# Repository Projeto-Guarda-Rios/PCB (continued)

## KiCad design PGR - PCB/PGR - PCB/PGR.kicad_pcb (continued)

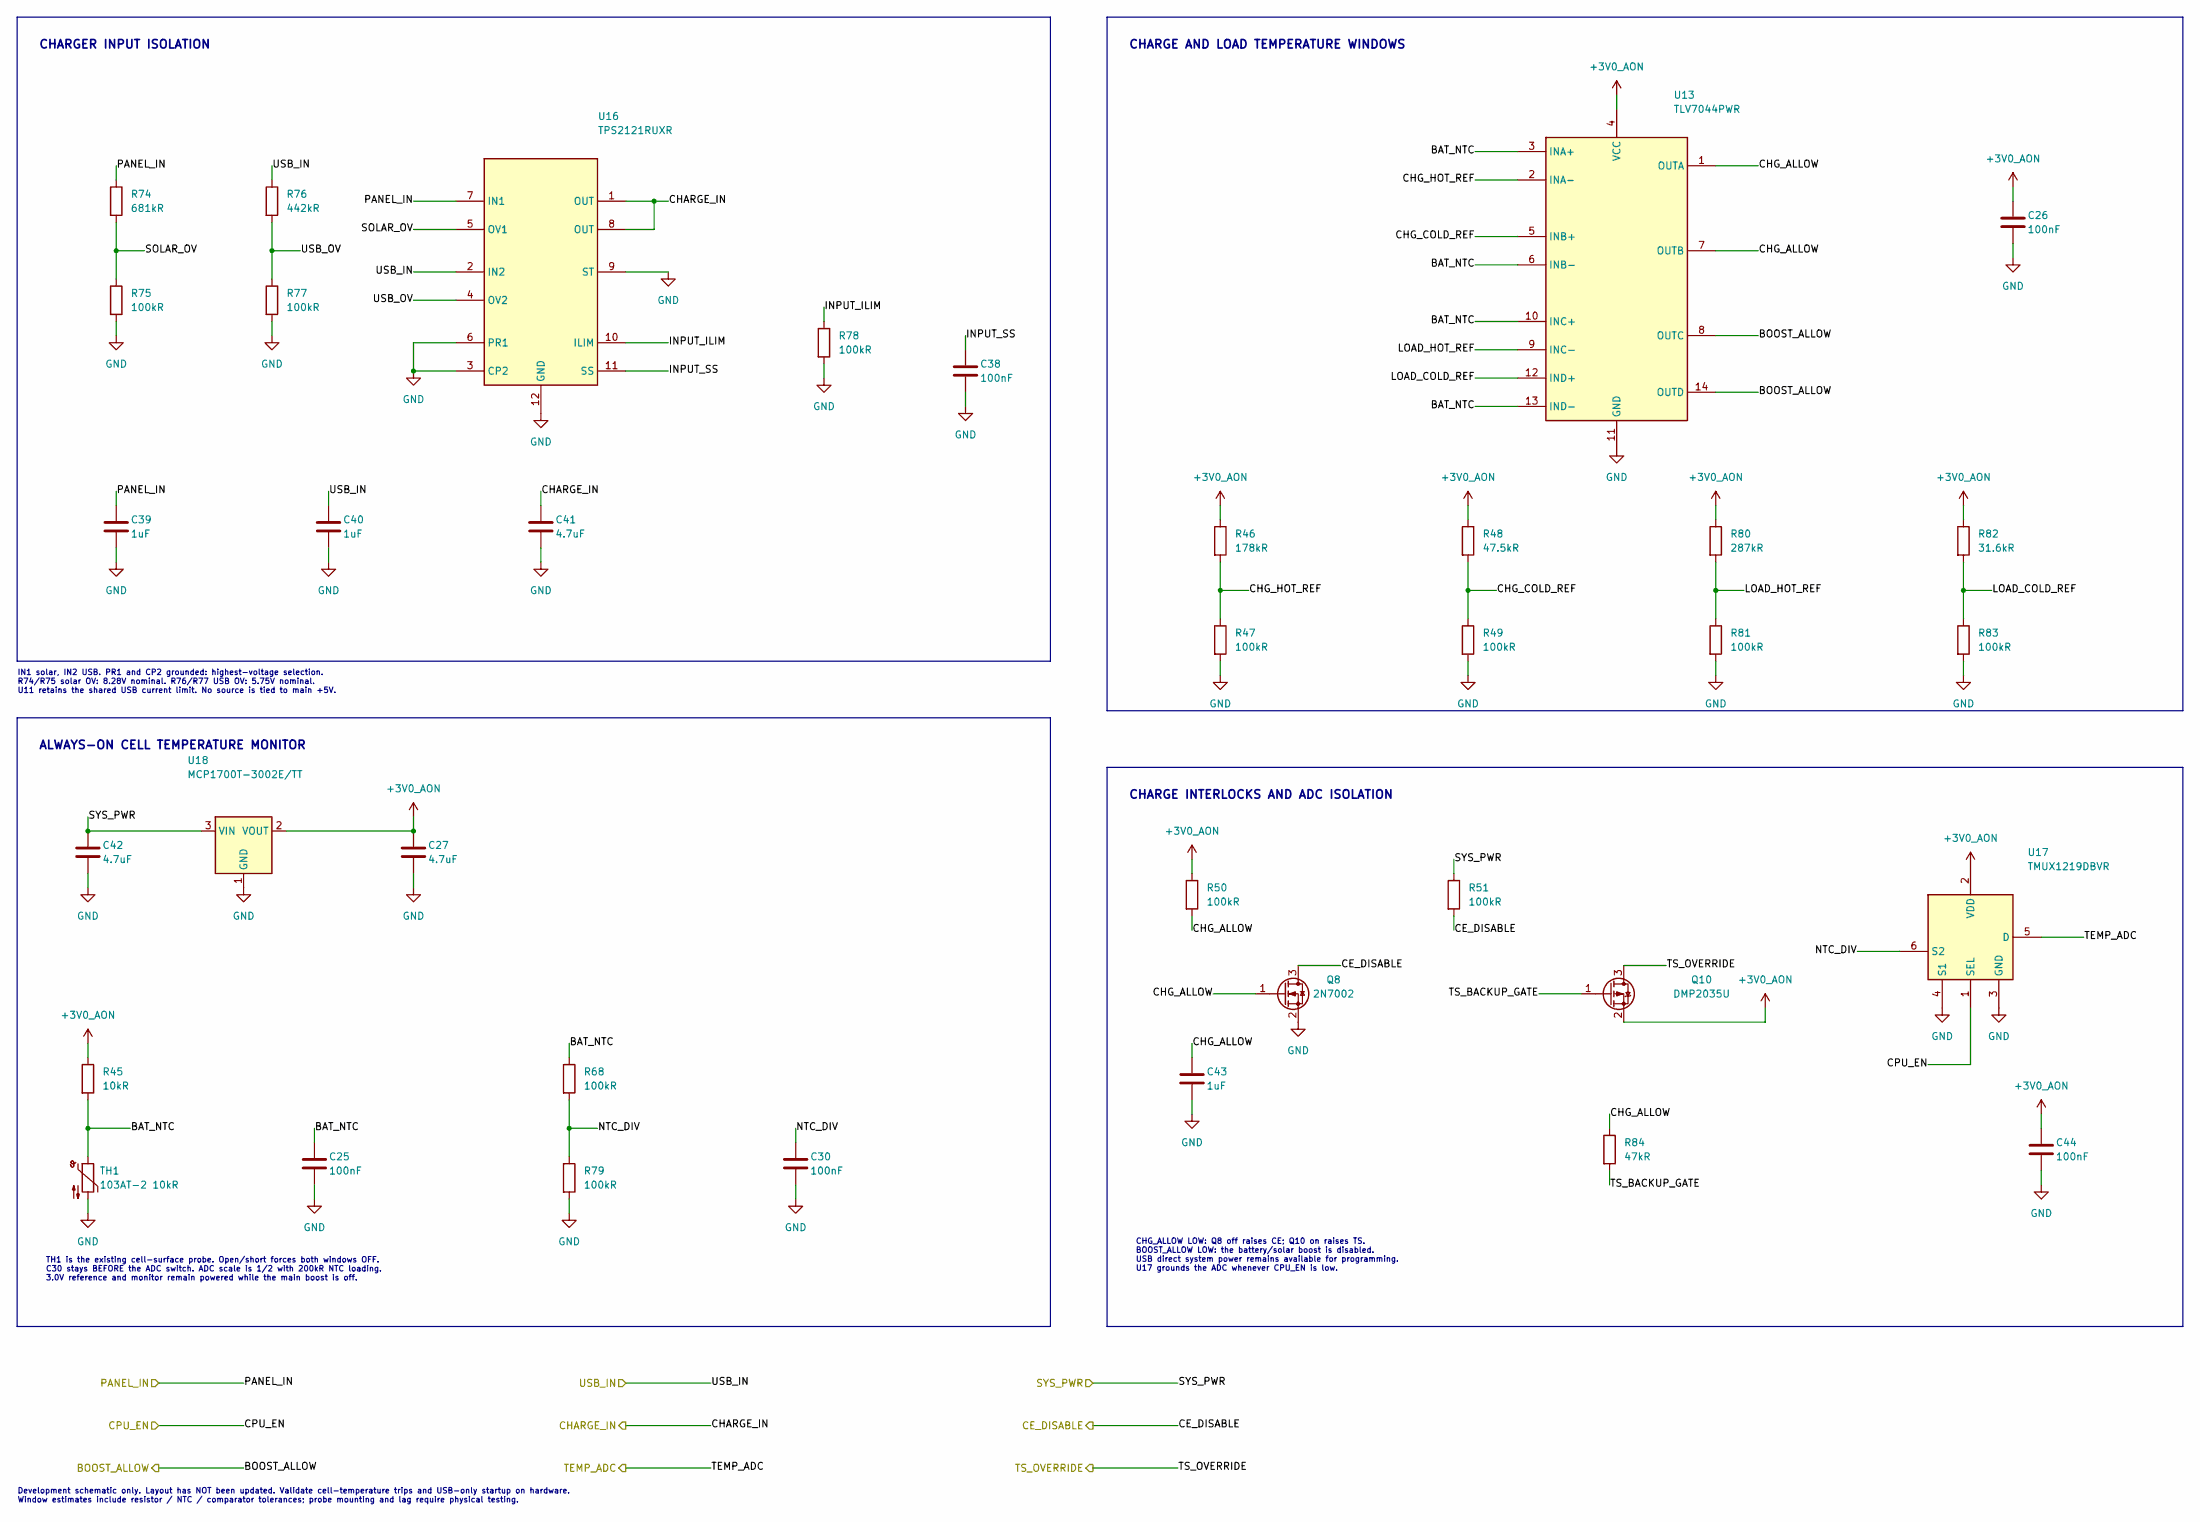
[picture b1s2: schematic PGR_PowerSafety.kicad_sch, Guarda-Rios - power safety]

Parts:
C25, C26, C30, C38, C44: 100nF; C_0603_1608Metric; Voltage Rating 16V minimum; Tolerance 10%
C27, C41, C42: 4.7uF; C_0805_2012Metric; Voltage Rating 10V minimum; Tolerance 10%
C39, C40, C43: 1uF; C_0805_2012Metric; Voltage Rating 10V minimum; Tolerance 10%
Q8: 2N7002; SOT-23; MPN 2N7002-7-F
Q10: DMP2035U; SOT-23; MPN DMP2035U-7
R45: 10kR; R_0603_1608Metric; Tolerance 0.1%; Power Rating 0.1W minimum
R46: 178kR; R_0603_1608Metric; Tolerance 0.1%; Power Rating 0.1W minimum
R47, R49, R68, R75, R77, R79, R81, R83: 100kR; R_0603_1608Metric; Tolerance 0.1%; Power Rating 0.1W minimum
R48: 47.5kR; R_0603_1608Metric; Tolerance 0.1%; Power Rating 0.1W minimum
R50, R51, R78: 100kR; R_0603_1608Metric; Tolerance 1%; Power Rating 0.1W minimum
R74: 681kR; R_0603_1608Metric; Tolerance 0.1%; Power Rating 0.1W minimum
R76: 442kR; R_0603_1608Metric; Tolerance 0.1%; Power Rating 0.1W minimum
R80: 287kR; R_0603_1608Metric; Tolerance 0.1%; Power Rating 0.1W minimum
R82: 31.6kR; R_0603_1608Metric; Tolerance 0.1%; Power Rating 0.1W minimum
R84: 47kR; R_0603_1608Metric; Tolerance 1%; Power Rating 0.1W minimum
TH1: 103AT-2 10kR; NTC_Semitec_103AT-2_P2.54mm; R25 Tolerance 1%; MPN 103AT-2; LCSC C5346323
U13: TLV7044PWR; TSSOP-14_4.4x5mm_P0.65mm; MPN TLV7044PWR
U16: TPS2121RUXR; Texas_VQFN-HR-12_2x2.5mm_P0.5mm; MPN TPS2121RUXR
U17: TMUX1219DBVR; SOT-23-6; MPN TMUX1219DBVR
U18: MCP1700T-3002E/TT; SOT-23; MPN MCP1700T-3002E/TT

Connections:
+3V0_AON: C26.1, C27.1, C44.1, Q10.2 (S), R45.1, R46.1, R48.1, R50.1, R80.1, R82.1, U13.4 (VCC), U17.2 (VDD), U18.2 (VOUT)
/Power safety/BAT_NTC: C25.1, R45.2, R68.1, TH1.1, U13.3 (INA+), U13.6 (INB-), U13.10 (INC+), U13.13 (IND-)
/Power safety/CHG_ALLOW: C43.1, Q8.1 (G), R50.2, R84.1, U13.1 (OUTA), U13.7 (OUTB)
/Power safety/CHG_COLD_REF: R48.2, R49.1, U13.5 (INB+)
/Power safety/CHG_HOT_REF: R46.2, R47.1, U13.2 (INA-)
/Power safety/INPUT_ILIM: R78.1, U16.10 (ILIM)
/Power safety/INPUT_SS: C38.1, U16.11 (SS)
/Power safety/LOAD_COLD_REF: R82.2, R83.1, U13.12 (IND+)
/Power safety/LOAD_HOT_REF: R80.2, R81.1, U13.9 (INC-)
/Power safety/NTC_DIV: C30.1, R68.2, R79.1, U17.6 (S2)
/Power safety/SOLAR_OV: R74.2, R75.1, U16.5 (OV1)
/Power safety/TS_BACKUP_GATE: Q10.1 (G), R84.2
/Power safety/USB_OV: R76.2, R77.1, U16.4 (OV2)
BOOST_EN: U13.8 (OUTC), U13.14 (OUTD); also elsewhere on the board
CHARGER_IN: C41.1, U16.1 (OUT), U16.8 (OUT); also elsewhere on the board
CHG_CE: Q8.3 (D), R51.2; also elsewhere on the board
EN: U17.1 (SEL); also elsewhere on the board
GND: C25.2, C26.2, C27.2, C30.2, C38.2, C39.2, C40.2, C41.2, C42.2, C43.2, C44.2, Q8.2 (S), R47.2, R49.2, R75.2, R77.2, R78.2, R79.2, R81.2, R83.2, TH1.2, U13.11 (GND), U16.3 (CP2), U16.6 (PR1), U16.9 (ST), U16.12 (GND), U17.3 (GND), U17.4 (S1), U18.1 (GND); also elsewhere on the board
NTC_ADC: U17.5 (D); also elsewhere on the board
PWR_OUT: C42.1, R51.1, U18.3 (VIN); also elsewhere on the board
SOLAR_PROTECTED: C39.1, R74.1, U16.7 (IN1); also elsewhere on the board
TS_FIXED: Q10.3 (D); also elsewhere on the board
USB_LIMIT: C40.1, R76.1, U16.2 (IN2); also elsewhere on the board

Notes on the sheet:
CHARGE INTERLOCKS AND ADC ISOLATION
CHARGE AND LOAD TEMPERATURE WINDOWS
IN1 solar, IN2 USB. PR1 and CP2 grounded: highest-voltage selection. R74/R75 solar OV: 8.28V nominal. R76/R77 USB OV: 5.75V nominal. U11 retains the shared USB current limit. No source is tied to main +5V.
TH1 is the existing cell-surface probe. Open/short forces both windows OFF. C30 stays BEFORE the ADC switch. ADC scale is 1/2 with 200kR NTC loading. 3.0V reference and monitor remain powered while the main boost is off.
CHG_ALLOW LOW: Q8 off raises CE; Q10 on raises TS. BOOST_ALLOW LOW: the battery/solar boost is disabled. USB direct system power remains available for programming. U17 grounds the ADC whenever CPU_EN is low.
CHARGER INPUT ISOLATION
ALWAYS-ON CELL TEMPERATURE MONITOR
Development schematic only. Layout has NOT been updated. Validate cell-temperature trips and USB-only startup on hardware. Window estimates include resistor / NTC / comparator tolerances; probe mounting and lag require physical testing.

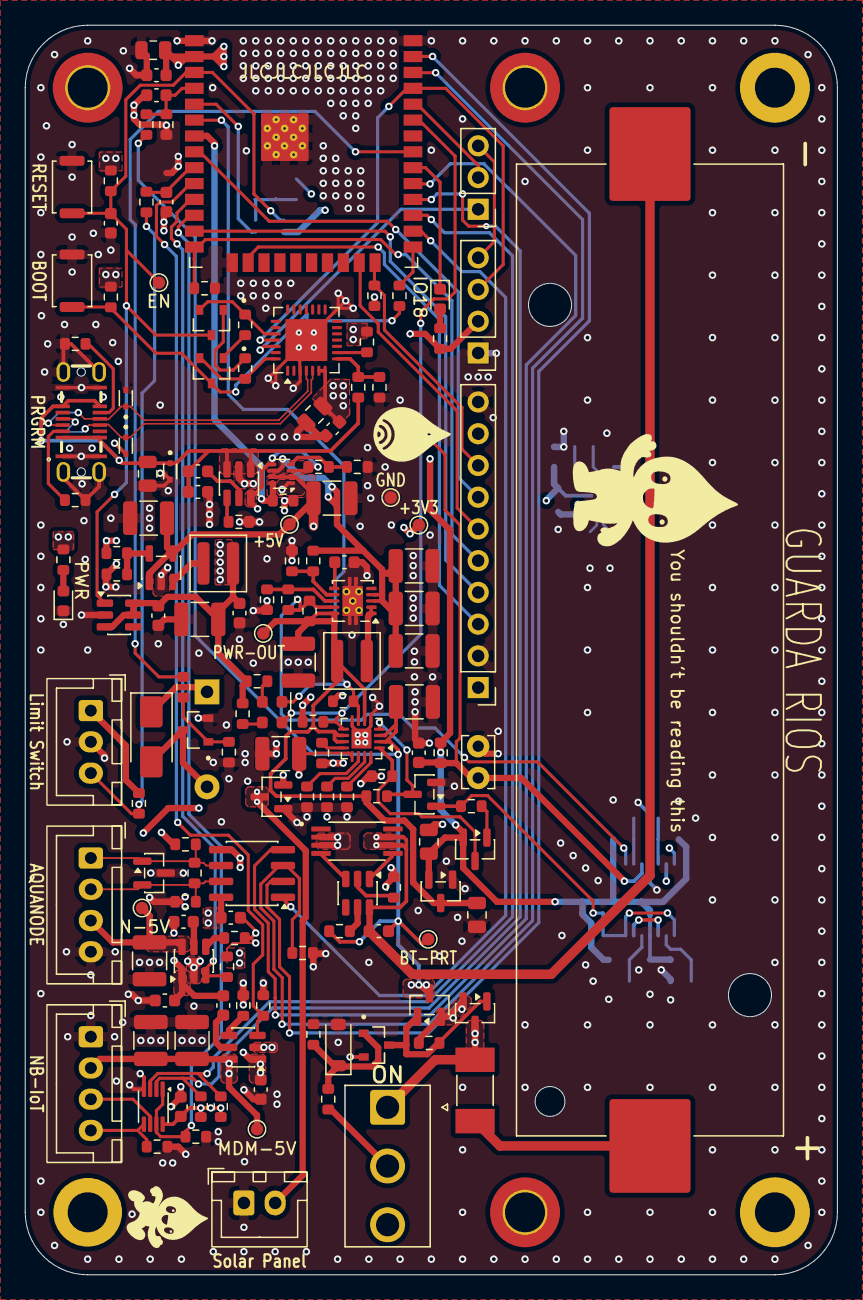
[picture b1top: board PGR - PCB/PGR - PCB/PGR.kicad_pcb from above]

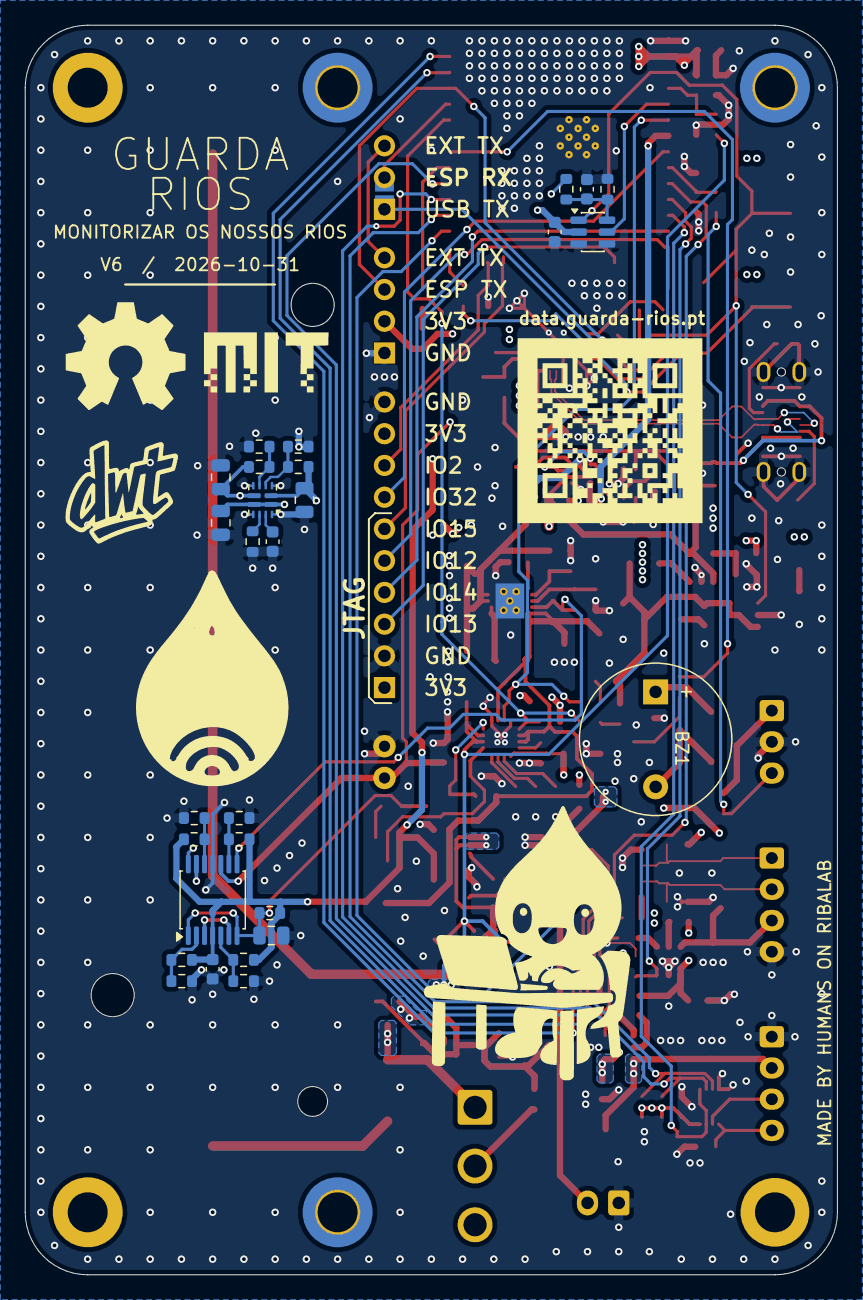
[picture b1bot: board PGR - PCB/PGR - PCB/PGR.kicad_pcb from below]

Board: 4 copper layers, 65.0 x 100.0 mm, 188 parts (29 on the bottom side), 108 nets.

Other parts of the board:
H1, H2, H5: MountingHole_3.2mm_M3_DIN965_Pad_TopBottom
H3, H6: MountingHole_3.2mm_M3_DIN965_Pad
H4: MountingHole_3.2mm_M3_ISO14580_Pad

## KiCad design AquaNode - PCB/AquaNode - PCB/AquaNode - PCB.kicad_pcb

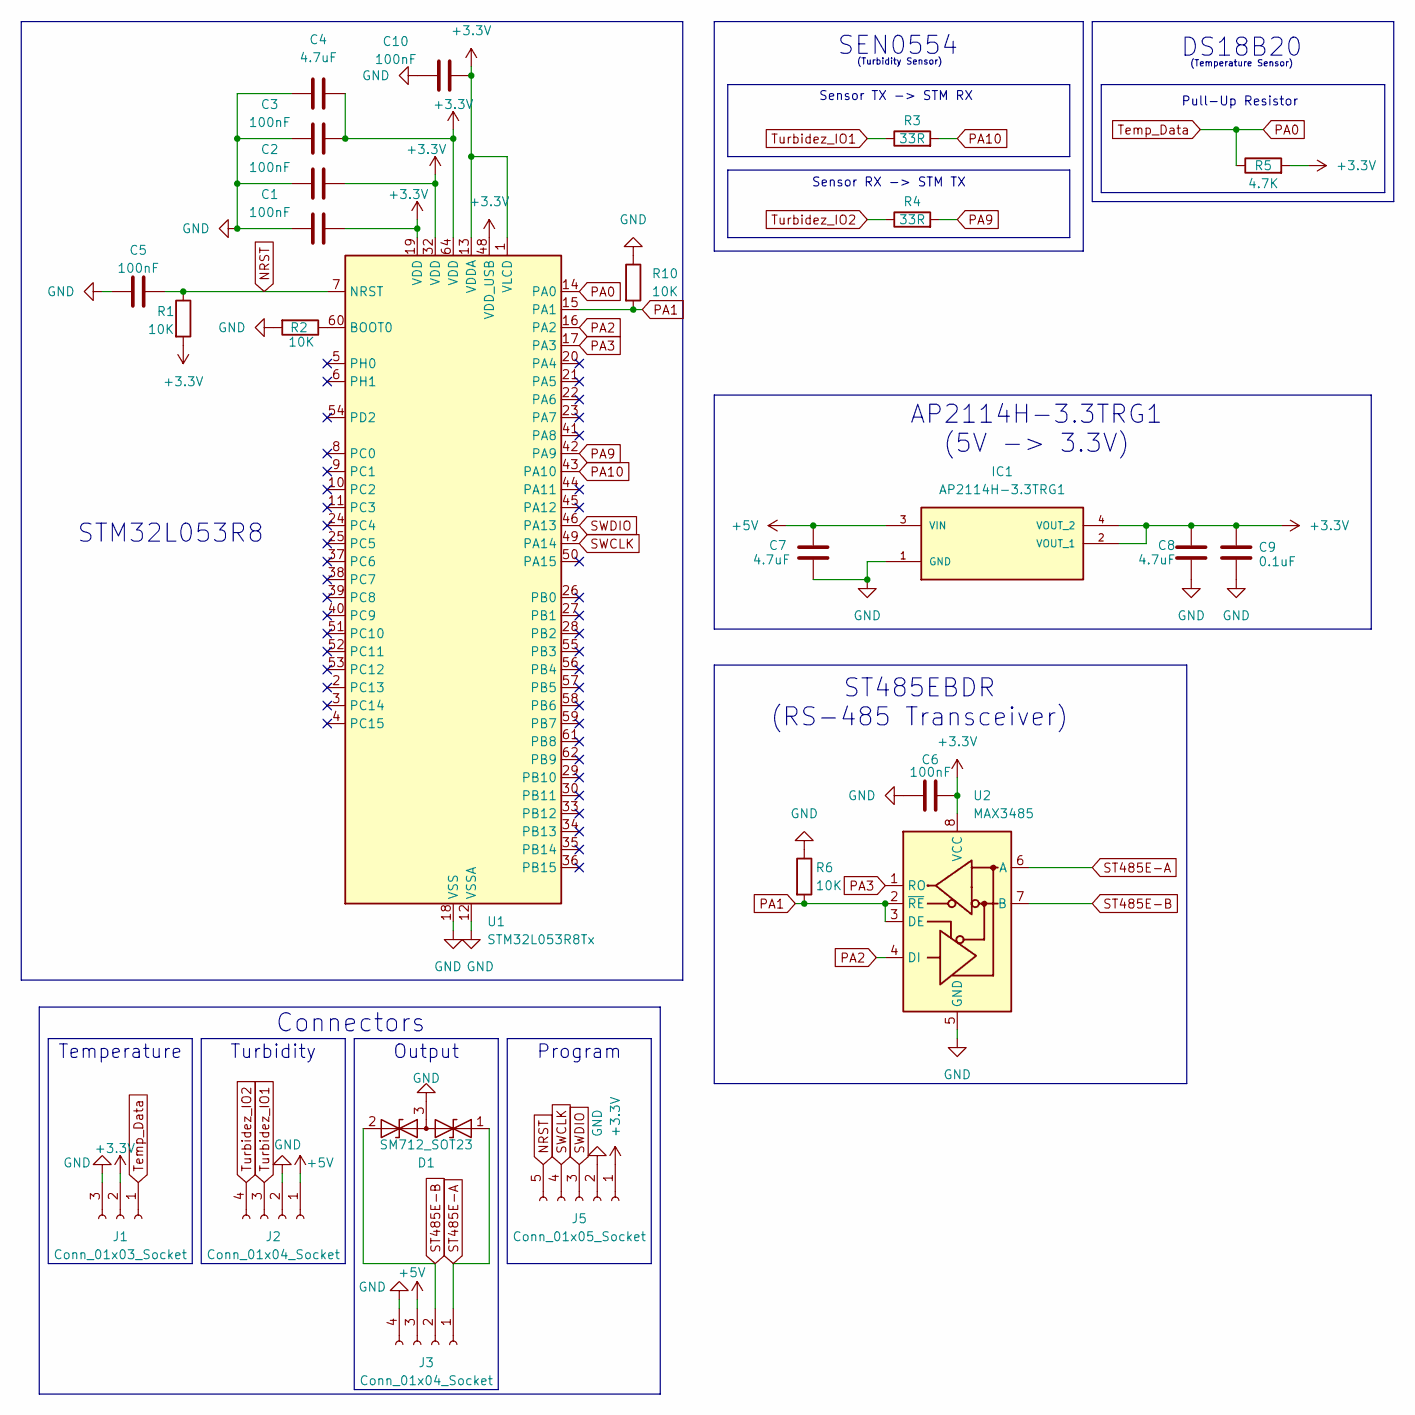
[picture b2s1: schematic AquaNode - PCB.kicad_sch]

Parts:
C1, C2, C3, C5, C6, C10: 100nF; C_0603_1608Metric
C4, C7, C8: 4.7uF; C_0603_1608Metric
C9: 0.1uF; C_0603_1608Metric
D1: SM712_SOT23; SOT-23
IC1: AP2114H-3.3TRG1; SOT230P700X180-4N; MANUFACTURER_PART_NUMBER AP2114H-3.3TRG1
J1: Conn_01x03_Socket; JST_EH_B3B-EH-A_1x03_P2.50mm_Vertical
J2, J3: Conn_01x04_Socket; JST_EH_B4B-EH-A_1x04_P2.50mm_Vertical
J5: Conn_01x05_Socket; PinHeader_1x05_P2.54mm_Vertical
R1, R2, R6, R10: 10K; R_0603_1608Metric
R3, R4: 33R; R_0603_1608Metric
R5: 4.7K; R_0603_1608Metric
U1: STM32L053R8Tx; LQFP-64_10x10mm_P0.5mm
U2: MAX3485; SOIC-8_3.9x4.9mm_P1.27mm

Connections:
+3.3V: C1.2, C2.2, C3.2, C4.2, C6.2, C8.1, C9.1, C10.2, IC1.2 (VOUT_1), IC1.4 (VOUT_2), J1.2, J5.1, R1.2, R5.2, U1.1 (VLCD), U1.13 (VDDA), U1.19 (VDD), U1.32 (VDD), U1.48 (VDD_USB), U1.64 (VDD), U2.8 (VCC)
+5V: C7.1, IC1.3 (VIN), J2.1, J3.3
GND: C1.1, C2.1, C3.1, C4.1, C5.1, C6.1, C7.2, C8.2, C9.2, C10.1, D1.3 (common), IC1.1 (GND), J1.3, J2.2, J3.4, J5.2, R2.2, R6.1, R10.1, U1.12 (VSSA), U1.18 (VSS), U1.31 (VSS), U1.47 (VSS), U1.63 (VSS), U2.5 (GND)
NRST: C5.2, J5.5, R1.1, U1.7 (NRST)
unnamed: R2.1, U1.60 (BOOT0)
PA0: J1.1, R5.1, U1.14 (PA0)
PA1: R6.2, R10.2, U1.15 (PA1), U2.2 (~RE), U2.3 (DE)
PA2: U1.16 (PA2), U2.4 (DI)
PA3: U1.17 (PA3), U2.1 (RO)
PA9: R4.2, U1.42 (PA9)
PA10: R3.2, U1.43 (PA10)
ST485E-A: D1.1 (A1), J3.1, U2.6 (A)
ST485E-B: D1.2 (A2), J3.2, U2.7 (B)
SWCLK: J5.4, U1.49 (PA14)
SWDIO: J5.3, U1.46 (PA13)
Turbidez_IO1: J2.3, R3.1
Turbidez_IO2: J2.4, R4.1

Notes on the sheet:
ST485EBDR (RS-485 Transceiver)
AP2114H-3.3TRG1 (5V -> 3.3V)
Program
DS18B20
Sensor RX -> STM TX
Output
Pull-Up Resistor
Connectors
Sensor TX -> STM RX
Temperature
SEN0554
(Temperature Sensor)
STM32L053R8
Turbidity
(Turbidity Sensor)

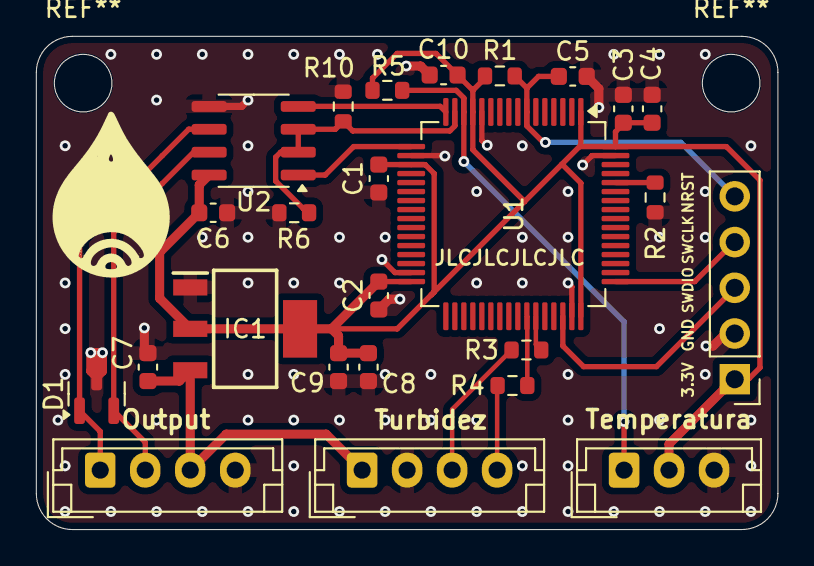
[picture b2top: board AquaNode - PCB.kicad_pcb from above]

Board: 2 copper layers, 41.2 x 27.4 mm, 25 parts (0 on the bottom side), 17 nets.

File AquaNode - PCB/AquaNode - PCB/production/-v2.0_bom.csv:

Designator,Footprint,Quantity,Value,LCSC Part #
"C1, C10, C2, C3, C5, C6",0603,6,100nF,
"C4, C7, C8",0603,3,4.7uF,
C9,0603,1,0.1uF,
D1,SOT-23,1,SM712_SOT23,
IC1,SOT230P700X180-4N,1,AP2114H-3.3TRG1,
J1,JST_EH_B3B-EH-A_1x03_P2.50mm_Vertical,1,Conn_01x03_Socket,
"J2, J3",JST_EH_B4B-EH-A_1x04_P2.50mm_Vertical,2,Conn_01x04_Socket,
J5,PinHeader_1x05_P2.54mm_Vertical,1,Conn_01x05_Socket,
"R1, R10, R2, R6",0603,4,10K,
R3,0603,1,1.8K,
R4,0603,1,3.3K,
R5,0603,1,4.7K,
U1,LQFP-64_10x10mm_P0.5mm,1,STM32L053R8Tx,
U2,SOIC-8_3.9x4.9mm_P1.27mm,1,MAX3485,

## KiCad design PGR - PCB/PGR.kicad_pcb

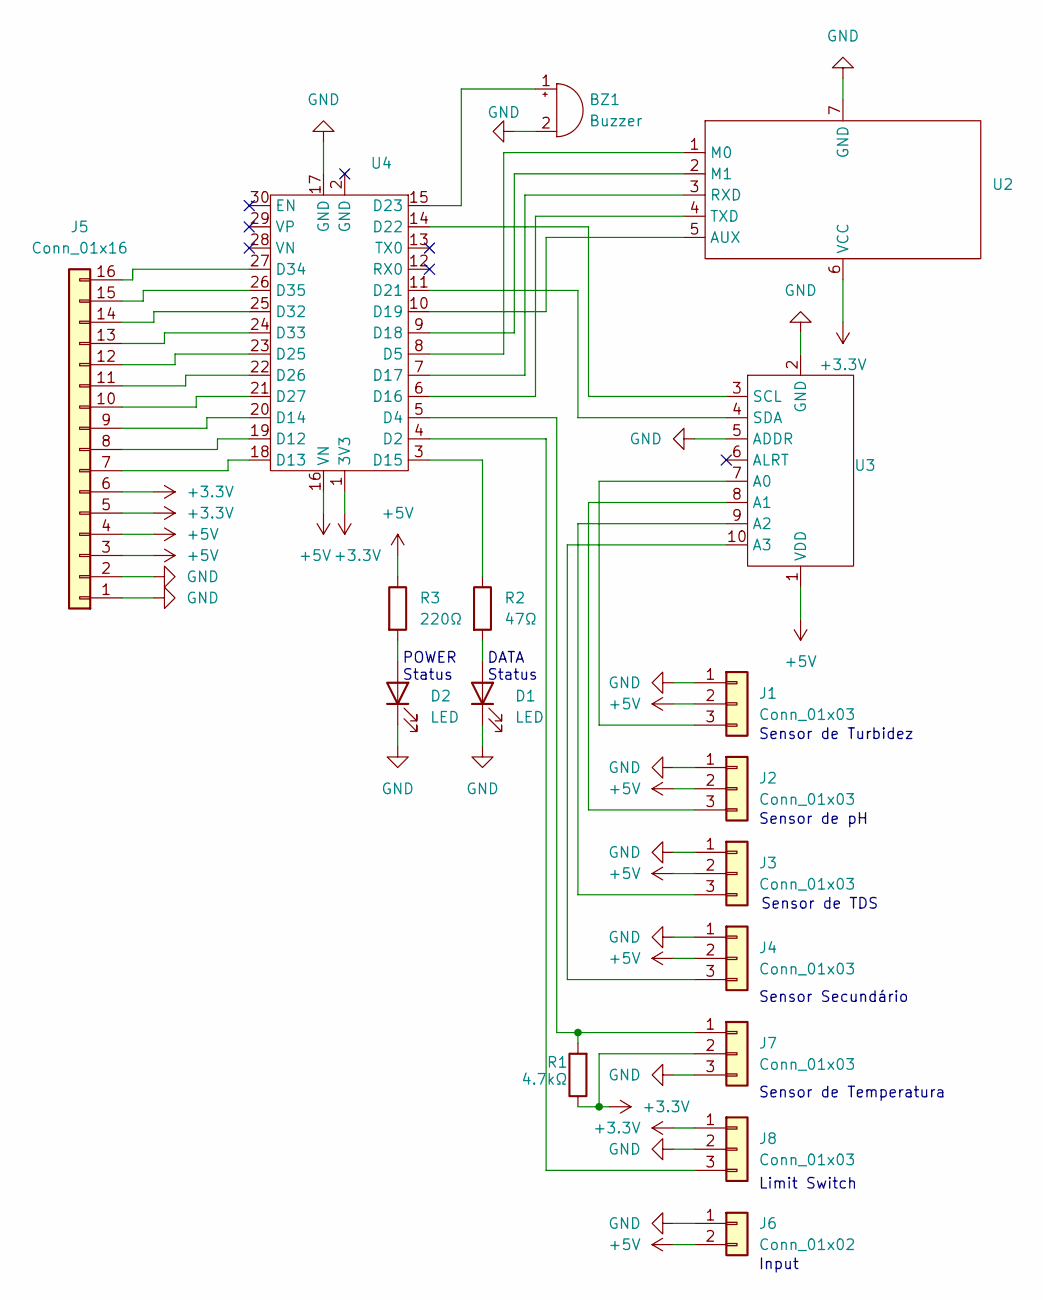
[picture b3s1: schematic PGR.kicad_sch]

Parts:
BZ1: Buzzer; Buzzer_12x9.5RM7.6
D1, D2: LED; LED_D3.0mm
J1, J2, J3, J4, J7, J8: Conn_01x03; JST_XH_B3B-XH-A_1x03_P2.50mm_Vertical
J5: Conn_01x16; PinSocket_1x16_P2.00mm_Vertical
J6: Conn_01x02; JST_XH_B2B-XH-A_1x02_P2.50mm_Vertical
R1: 4.7kΩ; R_Axial_DIN0204_L3.6mm_D1.6mm_P5.08mm_Horizontal
R2: 47Ω; R_Axial_DIN0204_L3.6mm_D1.6mm_P5.08mm_Horizontal
R3: 220Ω; R_Axial_DIN0204_L3.6mm_D1.6mm_P5.08mm_Horizontal
U2: PE32-90030D
U3: Adafruit_ADS1115
U4: ESP32-WROOM-32D - Board

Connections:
+3.3V: J5.5, J5.6, J7.2, J8.1, R1.1, U2.6 (VCC), U4.1 (3V3)
+5V: J1.2, J2.2, J3.2, J4.2, J5.3, J5.4, J6.2, R3.1, U3.1 (VDD), U4.16 (VN)
GND: BZ1.2 (-), D1.1 (K), D2.1 (K), J1.1, J2.1, J3.1, J4.1, J5.1, J5.2, J6.1, J7.3, J8.2, U2.7 (GND), U3.2 (GND), U3.5 (ADDR), U4.17 (GND)
unnamed: BZ1.1 (+), U4.15 (D23)
unnamed: D1.2 (A), R2.2
unnamed: D2.2 (A), R3.2
unnamed: J1.3, U3.7 (A0)
unnamed: J2.3, U3.8 (A1)
unnamed: J3.3, U3.9 (A2)
unnamed: J4.3, U3.10 (A3)
unnamed: J5.7, U4.18 (D13)
unnamed: J5.8, U4.19 (D12)
unnamed: J5.9, U4.20 (D14)
unnamed: J5.10, U4.21 (D27)
unnamed: J5.11, U4.22 (D26)
unnamed: J5.12, U4.23 (D25)
unnamed: J5.13, U4.24 (D33)
unnamed: J5.14, U4.25 (D32)
unnamed: J5.15, U4.26 (D35)
unnamed: J5.16, U4.27 (D34)
unnamed: J7.1, R1.2, U4.5 (D4)
unnamed: J8.3, U4.4 (D2)
unnamed: U2.5 (AUX), U4.10 (D19)
unnamed: U2.1 (M0), U4.8 (D5)
unnamed: U2.2 (M1), U4.9 (D18)
unnamed: U2.3 (RXD), U4.7 (D17)
unnamed: U2.4 (TXD), U4.6 (D16)
unnamed: U3.3 (SCL), U4.14 (D22)
unnamed: U3.4 (SDA), U4.11 (D21)
unnamed: R2.1, U4.3 (D15)

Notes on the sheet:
Sensor de pH
Sensor de TDS
Limit Switch
Sensor de Temperatura
Sensor Secundário
POWER Status
Sensor de Turbidez
DATA Status
Input

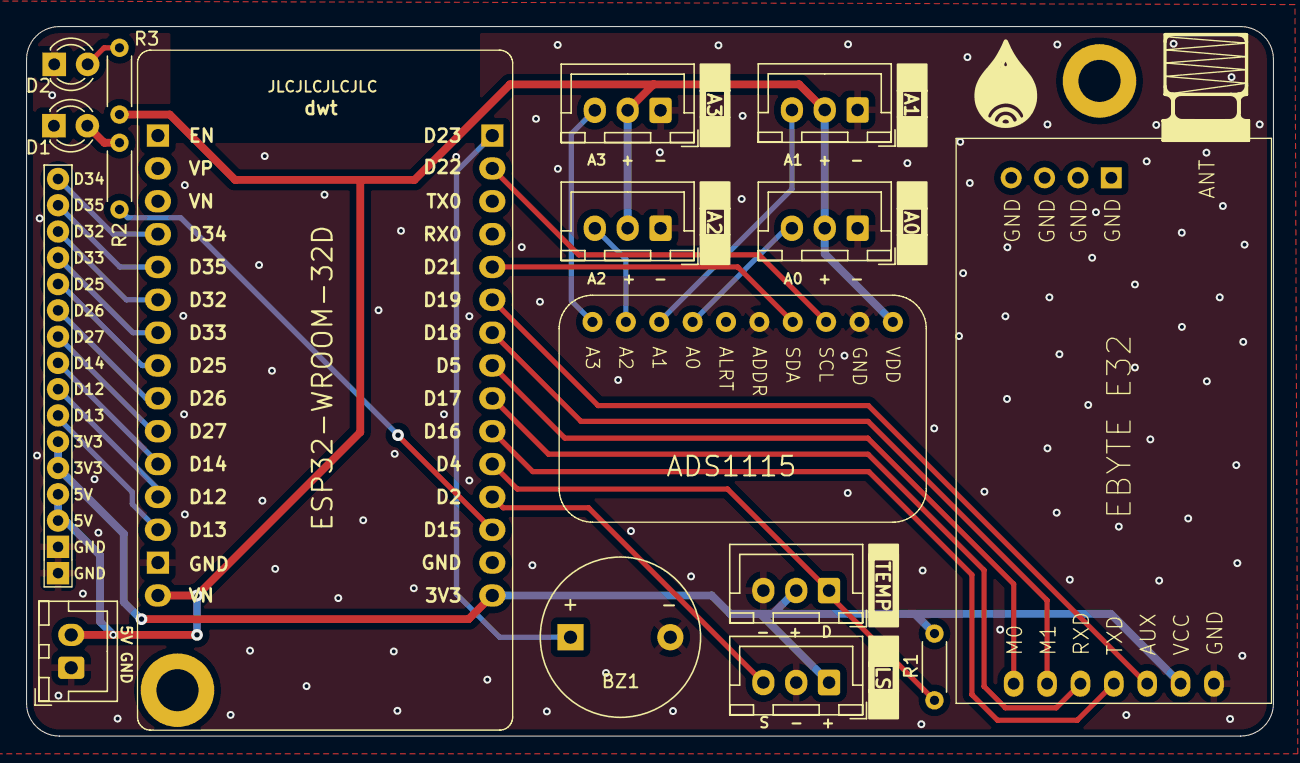
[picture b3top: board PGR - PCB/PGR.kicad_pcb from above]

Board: 2 copper layers, 94.9 x 54.0 mm, 17 parts (0 on the bottom side), 30 nets.

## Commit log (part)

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2025-05-18 Initial Commit🎉
    Adicionado os arquivos da PCB
2025-05-28 Adicionado um refresh button dos gráficos...
2026-03-22 Updated the PCBs to the most recent ones!
